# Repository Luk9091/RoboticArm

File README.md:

<span class='pageNumber'></span>
<span class='totalPages'></span>
# Robotic Arm
Poniższy projekt przedstawia roboramie, wykonane w ramach projektu zaliczeniowego na przedmiot `Systemy mikroprocesorowe II`.

## Wstęp
Tematem projektu jest robotyczne ramie, z możliwością sterowania po HTTP,
Ramie, zostało wydrukowane z projektu: *<p>https://www.thingiverse.com/thing:1015238</p>*

Sterowaniem zajmuje się mikroprocesor RP2040 z modułem Wi-Fi cyw43.
A projekt rozłożony jest między dwa języki *C* i *JavaScript*.
* W języku *C*, zbudowana została aplikacja na µP, która zawiera niskopoziomowe algorytmy sterowania silnikami, wykrywania przeciążeń serw oraz poprzez moduł Wi-Fi łączy się z siecią domową i wystawia stronę HTTP, będącą HID.
* Język *JS*, odpowiada, za rysowanie aktualnej pozycji ramienia, wyznaczenie położenia w osiach XYZ oraz odczytanie i wysłanie wartości kątów, jakie mają być ustawione w ramieniu.

# Build
!!! ***Wszystkie operację należy wykonywać w pliku `Src`*** !!!

Aby zbudować projekt należy:

1. Stworzyć pliki strony internetowej
```bash
$ python makefsdata.py
```
2. W pliku `main.c`, należy nadać NAZWĘ i HASŁO do sieci, z którą chcemy aby połączyła się malinka
```c
18 #include "PASS.h"
19 #ifndef SSID
20 #define SSID mySSID // Enter yours SSID
21 #define PASS myPASS // Enter yours PASSWORD
22 #endif
```
Alternatywnie w dowolnym folderze `Src`, można stworzyć plik `PASS.h`, w którym należy zadeklarować SSID oraz PASS
```c
#define SSID mySSID // Enter yours SSID
#define PASS myPASS // Enter yours PASSWORD
```
3. Zbudować projekt
```bash
$ mkdir -p build && cd $_
$ cmake ..
$ make
```
4. Wgrać projekt do płytki raspberry PI Pico W
```bash
$ cp build/main.uf2 /media/$USER/RPI-RP2
```

### Poprawne uruchomienie
Po poprawnej implementacji, Raspberry Pi PICO W powinno zapalić wbudowaną diodę, a na pinie `GPIO26` zostanie wygenerowany przebieg prostokątny o czestotliwosci ≈ 50Hz i  wypełnieniu 50%.

**Odczyt IP**:
Po połączeniu na terminalu podłączonym przez serial, zostanie przesłany adres IP.

Alternatywnie adres IP, można także sprawdzić w liście urządzeń na routerze.

### Błedy
Wszelkie błedy, które mogą wystąpić podczas uruchomienia, będą wyświetlane przez serial, a błędy krytyczne mogą zatrzymać cały proces.

| Nr | Komunikat | Oznaczenie błędu | Wyjaśnienie | Czy zatrzyma procesor |
|:---|:---------:|:----------------:|:-----------:|:---------------------:|
| 1. |WiFi module is init | ERR_OK  |Ponowna próba inicjalizacji WiFi| Nie |
| 2. |WiFi init failed    | ERR_CONN|Bład komunikacji między RP2040 a CYW43| TAK
| 3. |Cannot connected to `SSID` |ERR_CONN| Błąd podczas proby nawiązania połączenia z siecią WiFi | TAK|
| 4. |Open http server | ERR_OK | Zakończono proces łączenia z WiFi, a serwer HTTP został postawiony na przydzielonym adresie IP | Nie|
| 5. | Servo are init | ERR_OK | Ponowna próba inicjalizacji serw | Nie |
| 6. | Over current protection is turn on | ERR_OK | Ponowna próba włączenia ochrony przeciw przetężeniowej | Nie |

## Schemat

W schemacie układu można wyróżnić 4 główne bloki
- Raspberry Pi PICO W,
- zestaw 4 serwo mechanizmów,
- źródło napięcia referencyjnego,
- układ wykrywania przekroczenia prądu
    - 4 rezystory do pomiaru prądu,
    - 4 wzmacniacze operacyjne, mierzące spadek napięcia na rezystancji pomiarowej,
    - 4 komparatory, które porównują napięcie z wzmacniaczy z napięciem referencyjnym.

## Działanie
Użytkownik przez przeglądarkę łączy się z serwerem WWW stawianym przez malinkę.
Pozwala to na sterowanie każdym z silników, poprzez zadanie dozwolonego kąta.
W momencie, gdy któreś serwo nie może wykonać zadanego ruchu - zaczyna pobierać większy prąd, uruchamiany jest kilku sekundowy alarm.
Jeśli po zakończeniu alarmu serwo nadal pobiera duży prąd, silnik zostaje wyłączony* - a układ czeka na ponowne uruchomienie przez użytkownika.
Informacja o przeciążeniu zostaje oczywiście wysłane do użytkownika, poprzez stronę WWW.

*chwytak, nie zostaje wyłączony a jego zgięcie ograniczone jest do kąta, którego osiągnięcie jeszcze nie przekraczało wartości progowej.

# Pętle programu
```mermaid
stateDiagram

    [*]                      --> GlobalInit
    GlobalInit               --> StartHTTP
    StartHTTP                --> InBuildLED_ON
    InBuildLED_ON            --> servoMoveTo(servo.angle)
    servoMoveTo(servo.angle) --> run_OverCurrentTimer:if (servo.OverCurrent)
    run_OverCurrentTimer     --> servoMoveTo(servo.angle)
    servoMoveTo(servo.angle) --> servoMoveTo(servo.angle):else

    state run_OverCurrentTimer{
        [*]                      --> checkOverCurrent:wait
        checkOverCurrent         --> stopServo:if (overCurrent)
        stopServo                --> [*]
        checkOverCurrent         --> [*]
    }

    UserRefreshHTTP          --> sendWebPage
    UserSendDataByHTTP       --> servo.angle:storeNewAngel
```

# Podsumowanie
Projekt, jest udaną próbą stworzenia ramienia robota, pokazującym, że odpowiednia kontrola nawet tanich serwomechanizmów, pozwala na osiągnięcie jedno stopniowej precyzji.
Pomiar prądu w celu zabezpieczenia układu przed uszkodzeniem okazał się także strzałem w dziesiątkę. 
Ponieważ pozwala nie tylko odciążyć zasoby wbudowane w kontroler, ale także przy odpowiedniej regulacji ustroju pomiarowego możne określać czy silniki pracują poprawnie.
Przykładowo, można sprawdzić czy silnik jest podłączony - w trakcie normalnej pracy silniki zawsze pobierają minimum 10mA.

### Nie udało się zrealizować
Ostatecznie nie udało się odczytywać na bieżąco kata ustawionego na potencjometrze, ze względu na za duże wachania odczytanych wartości.
Zastosowanie znacznego uśredniania nie wchodzi w grę w momencie gdy układ ma pracować z szybkościami 100 deg/s.

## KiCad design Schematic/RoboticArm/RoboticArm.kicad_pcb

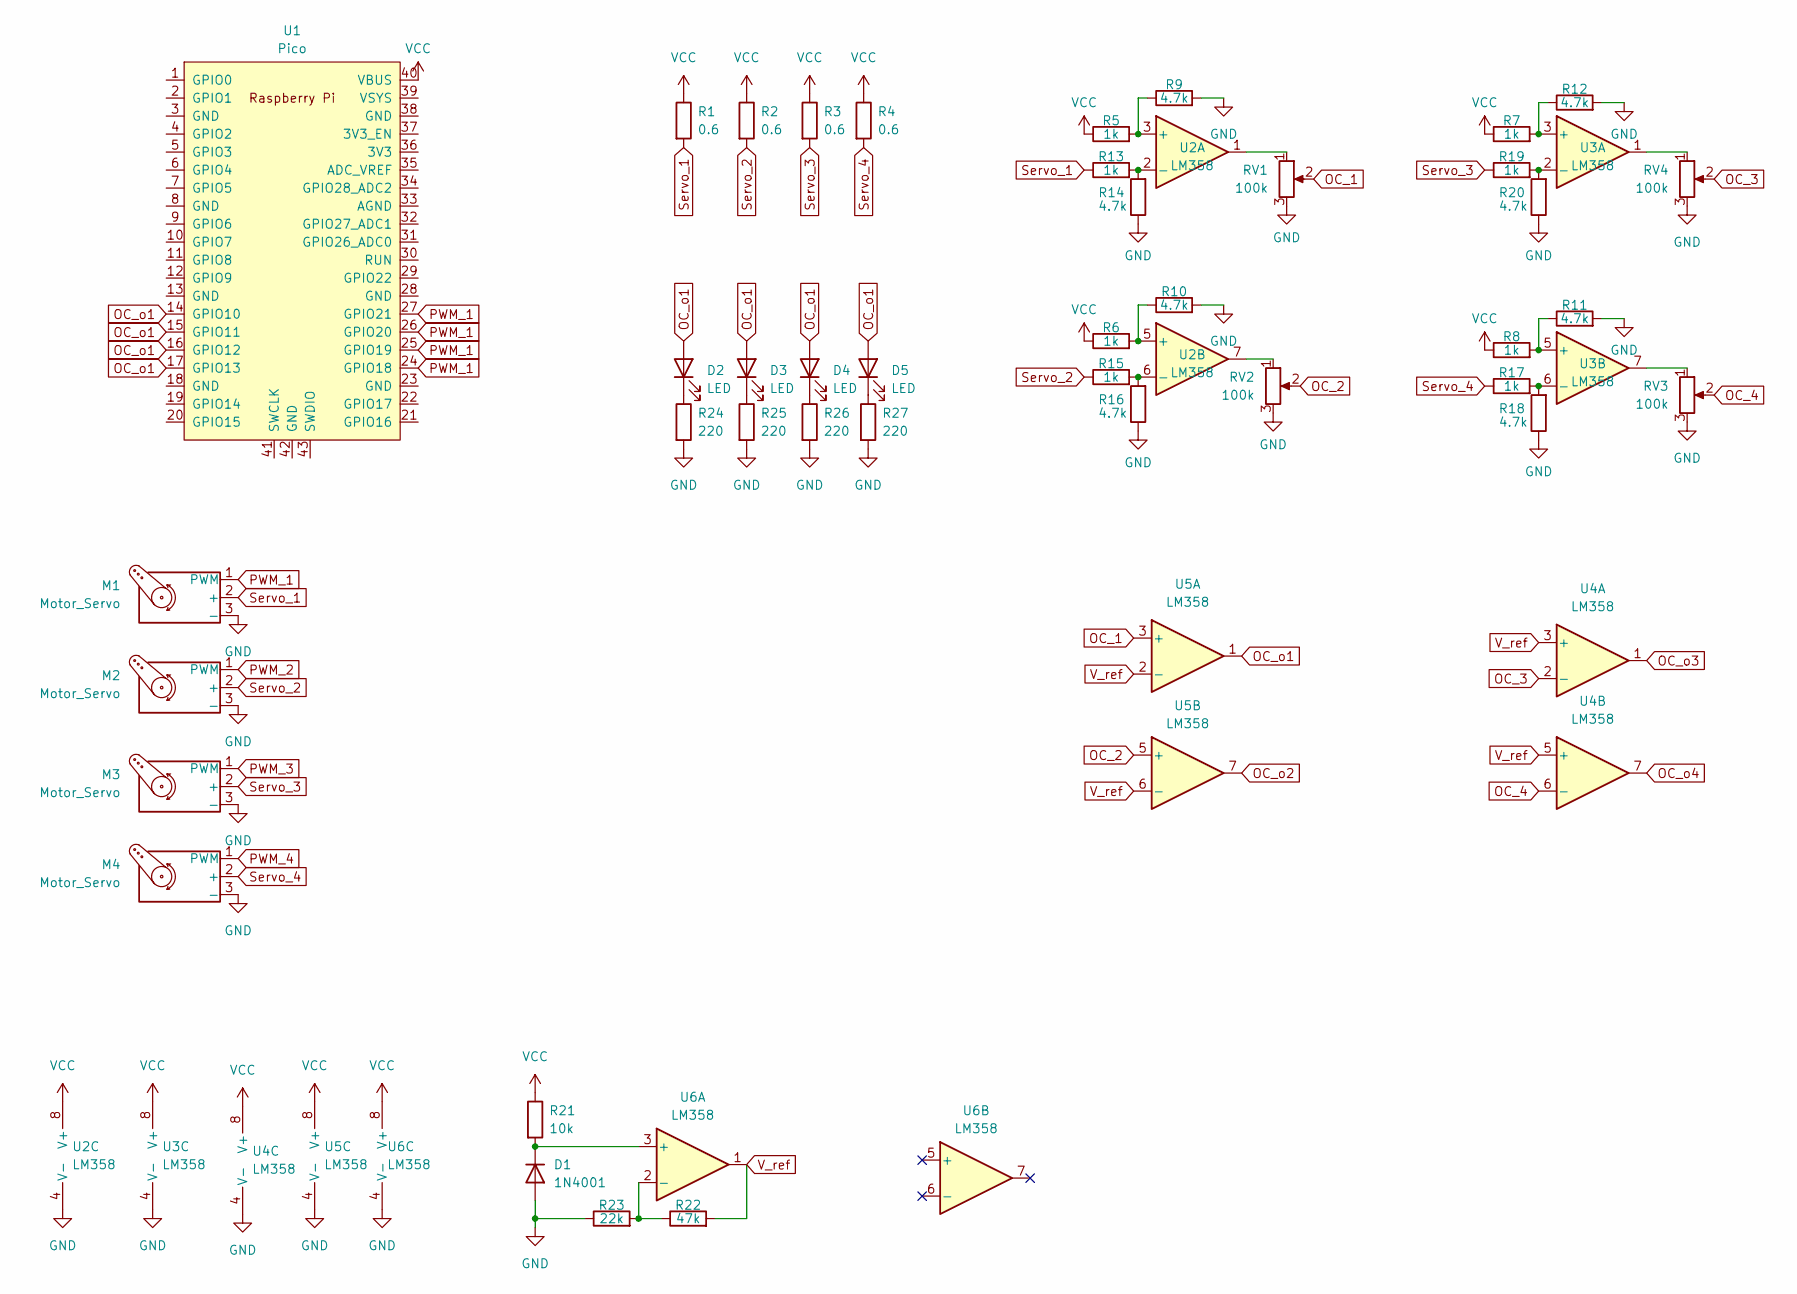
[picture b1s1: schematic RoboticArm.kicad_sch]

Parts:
D1: 1N4001; D_0805_2012Metric
D2, D3, D4, D5: LED; LED_D2.0mm_W4.8mm_H2.5mm_FlatTop
M1, M2, M3, M4: Motor_Servo; PinHeader_1x03_P2.54mm_Horizontal
R1, R2, R3, R4: 0.6; R_0805_2012Metric
R5, R6, R7, R8, R13, R15, R17, R19: 1k; R_0805_2012Metric
R9, R10, R11, R12, R14, R16, R18, R20: 4.7k; R_0805_2012Metric
R21: 10k; R_0805_2012Metric
R22: 47k; R_0805_2012Metric
R23: 22k; R_0805_2012Metric
R24, R25, R26, R27: 220; R_0805_2012Metric
RV1, RV2, RV3, RV4: 100k; R_0805_2012Metric
U1: Pico; RPi_Pico_SMD_TH
U2, U3, U4, U5, U6: LM358; SO-8_3.9x4.9mm_P1.27mm

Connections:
GND: D1.2 (A), M1.3 (-), M2.3 (-), M3.3 (-), M4.3 (-), R9.2, R10.2, R11.2, R12.2, R14.1, R16.1, R18.1, R20.1, R23.1, R24.2, R25.2, R26.2, R27.2, RV1.3, RV2.3, RV3.3, RV4.3, U2.4 (V-), U3.4 (V-), U4.4 (V-), U5.4 (V-), U6.4 (V-)
unnamed: D1.1 (K), R21.2, U6.3 (+)
unnamed: D2.1 (K), R24.1
unnamed: D3.1 (K), R25.1
unnamed: D4.1 (K), R26.1
unnamed: D5.1 (K), R27.1
unnamed: RV1.1, U2.1
unnamed: RV2.1, U2.7
unnamed: RV3.1, U3.7
unnamed: RV4.1, U3.1
unnamed: R5.2, R9.1, U2.3 (+)
unnamed: R13.2, R14.2, U2.2 (-)
unnamed: R6.2, R10.1, U2.5 (+)
unnamed: R15.2, R16.2, U2.6 (-)
unnamed: R7.2, R12.1, U3.3 (+)
unnamed: R19.2, R20.2, U3.2 (-)
unnamed: R8.2, R11.1, U3.5 (+)
unnamed: R17.2, R18.2, U3.6 (-)
unnamed: R22.1, R23.2, U6.2 (-)
OC_1: RV1.2, U5.3 (+)
OC_2: RV2.2, U5.5 (+)
OC_3: RV4.2, U4.2 (-)
OC_4: RV3.2, U4.6 (-)
OC_o1: D2.2 (A), D3.2 (A), D4.2 (A), D5.2 (A), U1.14 (GPIO10), U1.15 (GPIO11), U1.16 (GPIO12), U1.17 (GPIO13), U5.1
OC_o2: U5.7
OC_o3: U4.1
OC_o4: U4.7
PWM_1: M1.1 (PWM), U1.24 (GPIO18), U1.25 (GPIO19), U1.26 (GPIO20), U1.27 (GPIO21)
PWM_2: M2.1 (PWM)
PWM_3: M3.1 (PWM)
PWM_4: M4.1 (PWM)
Servo_1: M1.2 (+), R1.2, R13.1
Servo_2: M2.2 (+), R2.2, R15.1
Servo_3: M3.2 (+), R3.2, R19.1
Servo_4: M4.2 (+), R4.2, R17.1
VCC: R1.1, R2.1, R3.1, R4.1, R5.1, R6.1, R7.1, R8.1, R21.1, U1.40 (VBUS), U2.8 (V+), U3.8 (V+), U4.8 (V+), U5.8 (V+), U6.8 (V+)
V_ref: R22.2, U4.3 (+), U4.5 (+), U5.2 (-), U5.6 (-), U6.1

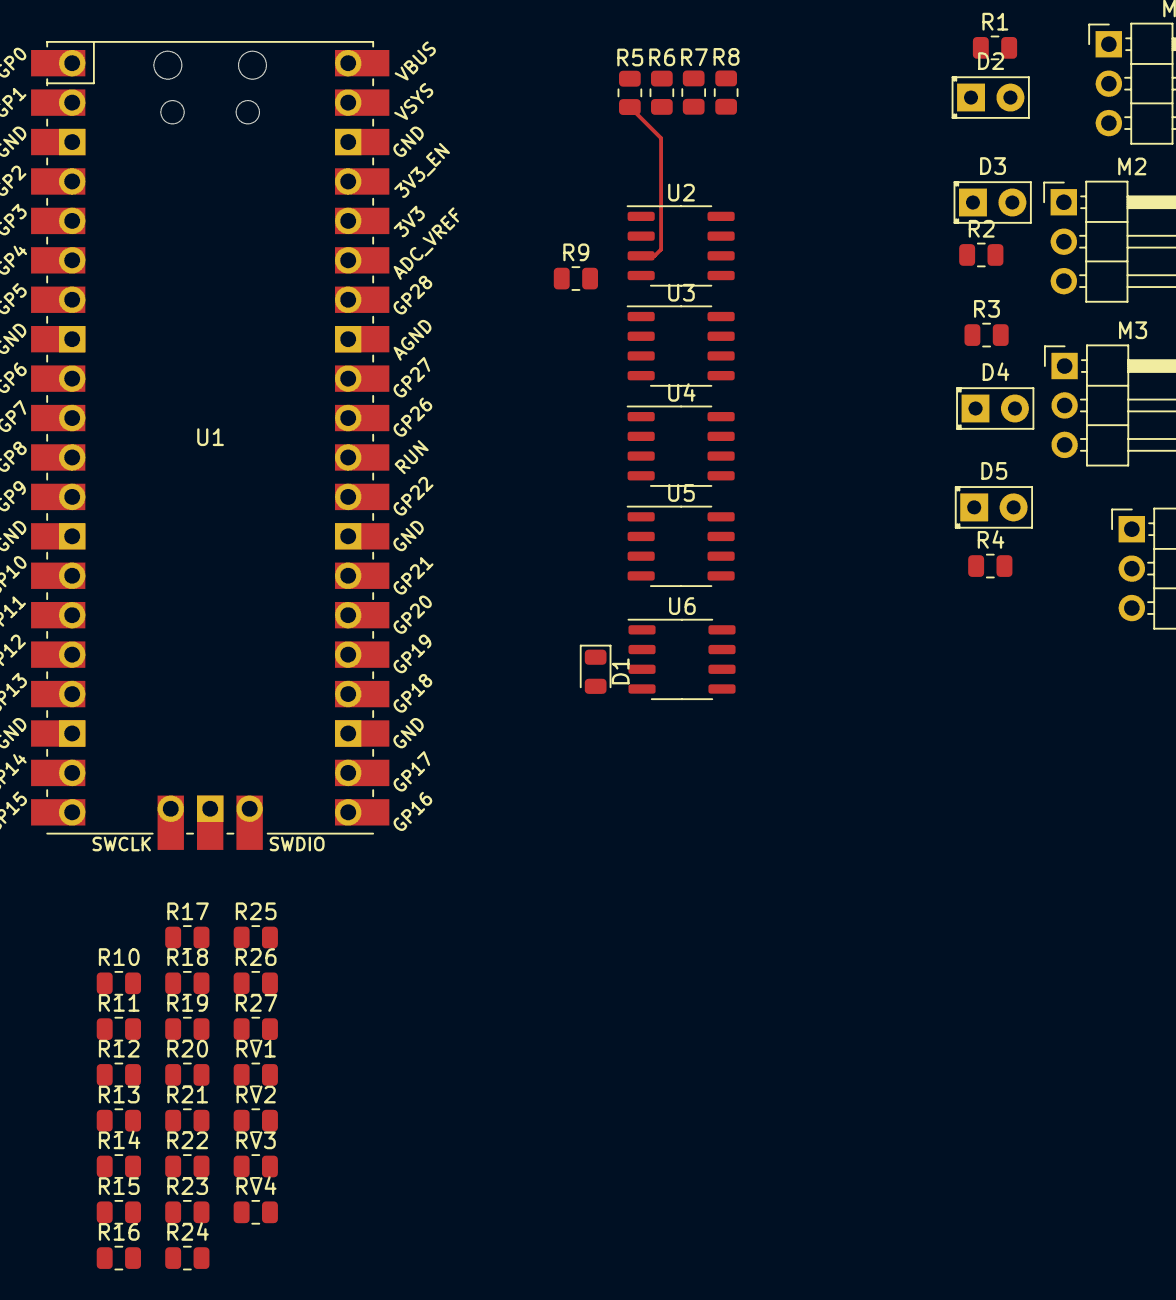
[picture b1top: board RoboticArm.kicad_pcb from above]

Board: 2 copper layers, 46 parts (0 on the bottom side), 31 nets.

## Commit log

2023-12-28 Add CrossBar and limit angle
2023-12-29 Add y adxis, constrol and show XY position
2023-12-29 Remove useless file
2024-01-16 Add web server -- without cgi sens
2024-01-16 Make web page
2024-01-16 Update commit -- WebServer
2024-01-16 Add step value
2024-01-17 Limit max angle
2024-01-17 Fix on load error
2024-01-17 Fix onload function
2024-01-18 Over current protection
2024-01-18 Web server send and receive
2024-01-18 Update file
2024-01-19 Auto reload
2024-01-19 Over current protection -- back to save angle
2024-01-21 Better update XYZ, set XYZ as readonly
2024-01-21 Cleaning
2024-01-21 Return SHTML tags
2024-01-22 Remove double line
2024-01-22 Fix OC index
2024-01-22 Update gitignore
2024-01-22 Make schematic
2024-01-23 Add pdf schematic
2024-01-23 Remove caches
2024-01-25 ReadME update
2024-01-25 Correcting typos
